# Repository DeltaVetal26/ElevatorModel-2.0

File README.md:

# ElevatorModel-2.0
Software and hardware for elevator model (STM32F3)

The first version of the elevator controller was assembled on the Arduino Pro Mini. Reed switches were used as floor sensors. The AC motor was controlled via a relay block.

The first version often freeze due to the lack of galvanic isolation

It was decided to develop a new version of the controller using galvanic isolation and based on the STM32F334K8T6 microcontroller.

Features:
1) The inputs on the board are isolated via optocouplers
2) The I2C bus responsible for outputting the current floor and reading the buttons is isolated through a digital isolator
3) A stepper motor is used as a drive
4) Optocouplers are used as floor sensors
5) The board has a step down converter (12V/3V3)

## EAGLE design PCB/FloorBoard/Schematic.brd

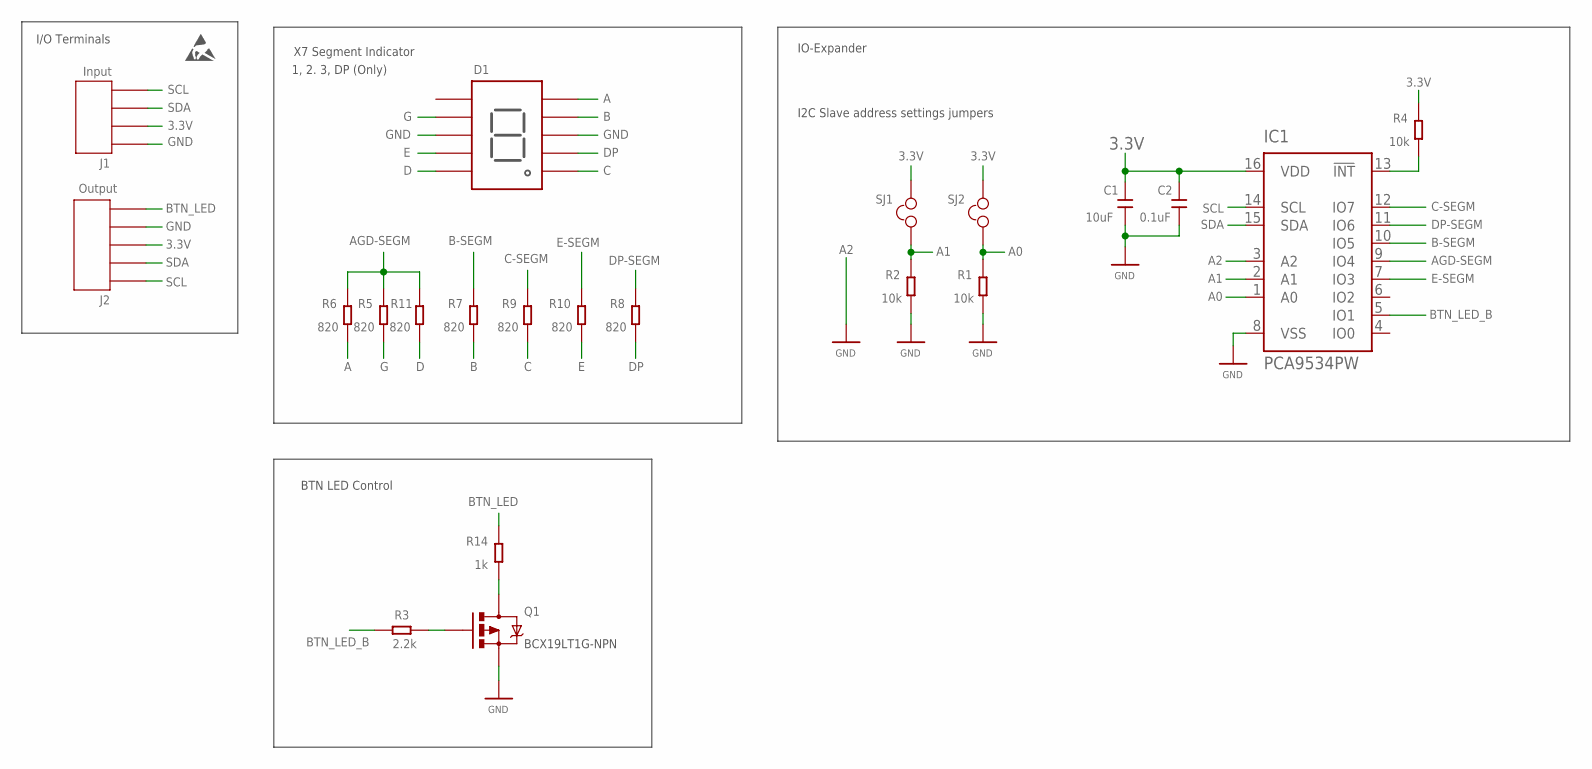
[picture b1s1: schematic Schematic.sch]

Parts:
C1: 10uF; SMD-CAP-0805
C2: 0.1uF; SMD-CAP-0805
D1: GNS-3011CS-21
IC1: PCA9534PW; TSSOP16
J1: Input; WF-4R
J2: Output; WF-5R
Q1: MOSFET-PCHANNEL; SOT23-3
R1, R2, R4: 10k; SMD-RES-0603
R3: 2.2k; SMD-RES-0603
R5, R6, R7, R8, R9, R10, R11: 820; SMD-RES-0603
R14: 1k; SMD-RES-0603
SJ1, SJ2: SOLDER-JUMPER
U$2: ESD-LOGO

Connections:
3.3V: C1.2, C2.2, IC1.16 (VDD), J1.P$2, J2.P$3, R4.2, SJ1.P$2, SJ2.P$2
A: D1.A, R6.1
A0: IC1.1 (A0), R1.2, SJ2.P$1
A1: IC1.2 (A1), R2.2, SJ1.P$1
A2: IC1.3 (A2)
AGD-SEGM: IC1.9 (IO4), R5.2, R6.2, R11.2
B: D1.B, R7.1
B-SEGM: IC1.10 (IO5), R7.2
BTN_LED: J2.P$5, R14.2
BTN_LED_B: IC1.5 (IO1), R3.2
C: D1.C, R9.1
C-SEGM: IC1.12 (IO7), R9.2
D: D1.D, R11.1
DP: D1.DP, R8.1
DP-SEGM: IC1.11 (IO6), R8.2
E: D1.E, R10.1
E-SEGM: IC1.7 (IO3), R10.2
G: D1.G, R5.1
GND: C1.1, C2.1, D1.CATHODE_1, D1.CATHODE_2, IC1.8 (VSS), J1.P$1, J2.P$4, Q1.2 (S), R1.1, R2.1
unnamed: IC1.13 (!INT), R4.1
unnamed: Q1.3 (D), R14.1
unnamed: Q1.1 (G), R3.1
SCL: IC1.14 (SCL), J1.P$4, J2.P$1
SDA: IC1.15 (SDA), J1.P$3, J2.P$2

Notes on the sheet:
I/O Terminals
X7 Segment Indicator
1, 2. 3, DP (Only)
IO-Expander
I2C Slave address settings jumpers
BCX19LT1G-NPN
BTN LED Control

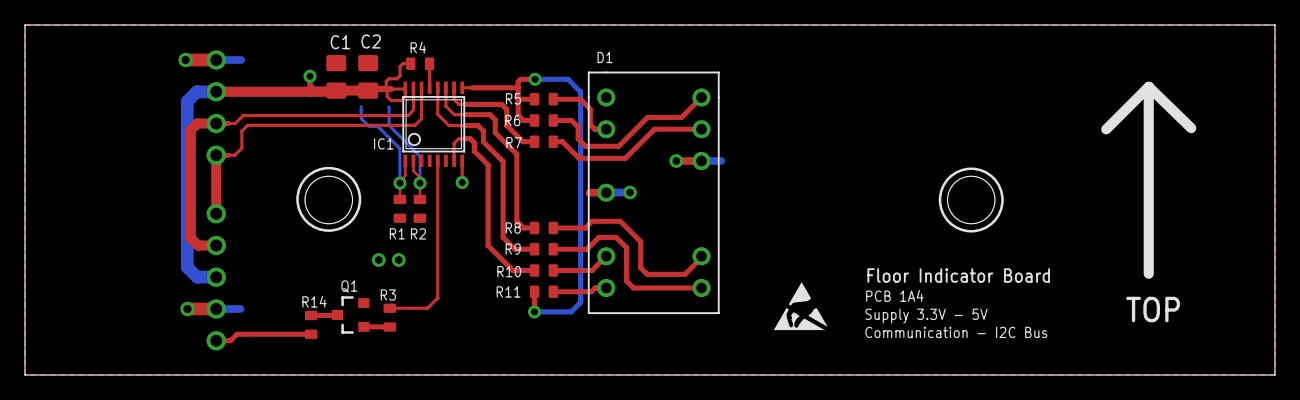
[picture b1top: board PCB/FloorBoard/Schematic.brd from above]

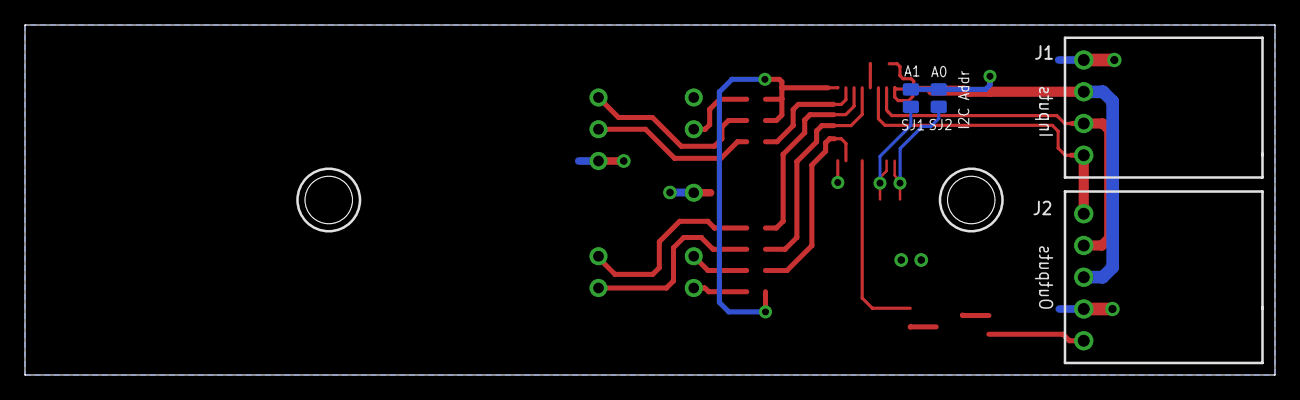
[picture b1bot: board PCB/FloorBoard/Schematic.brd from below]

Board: 2 copper layers, 100.0 x 28.0 mm, 22 parts (4 on the bottom side), 23 nets.

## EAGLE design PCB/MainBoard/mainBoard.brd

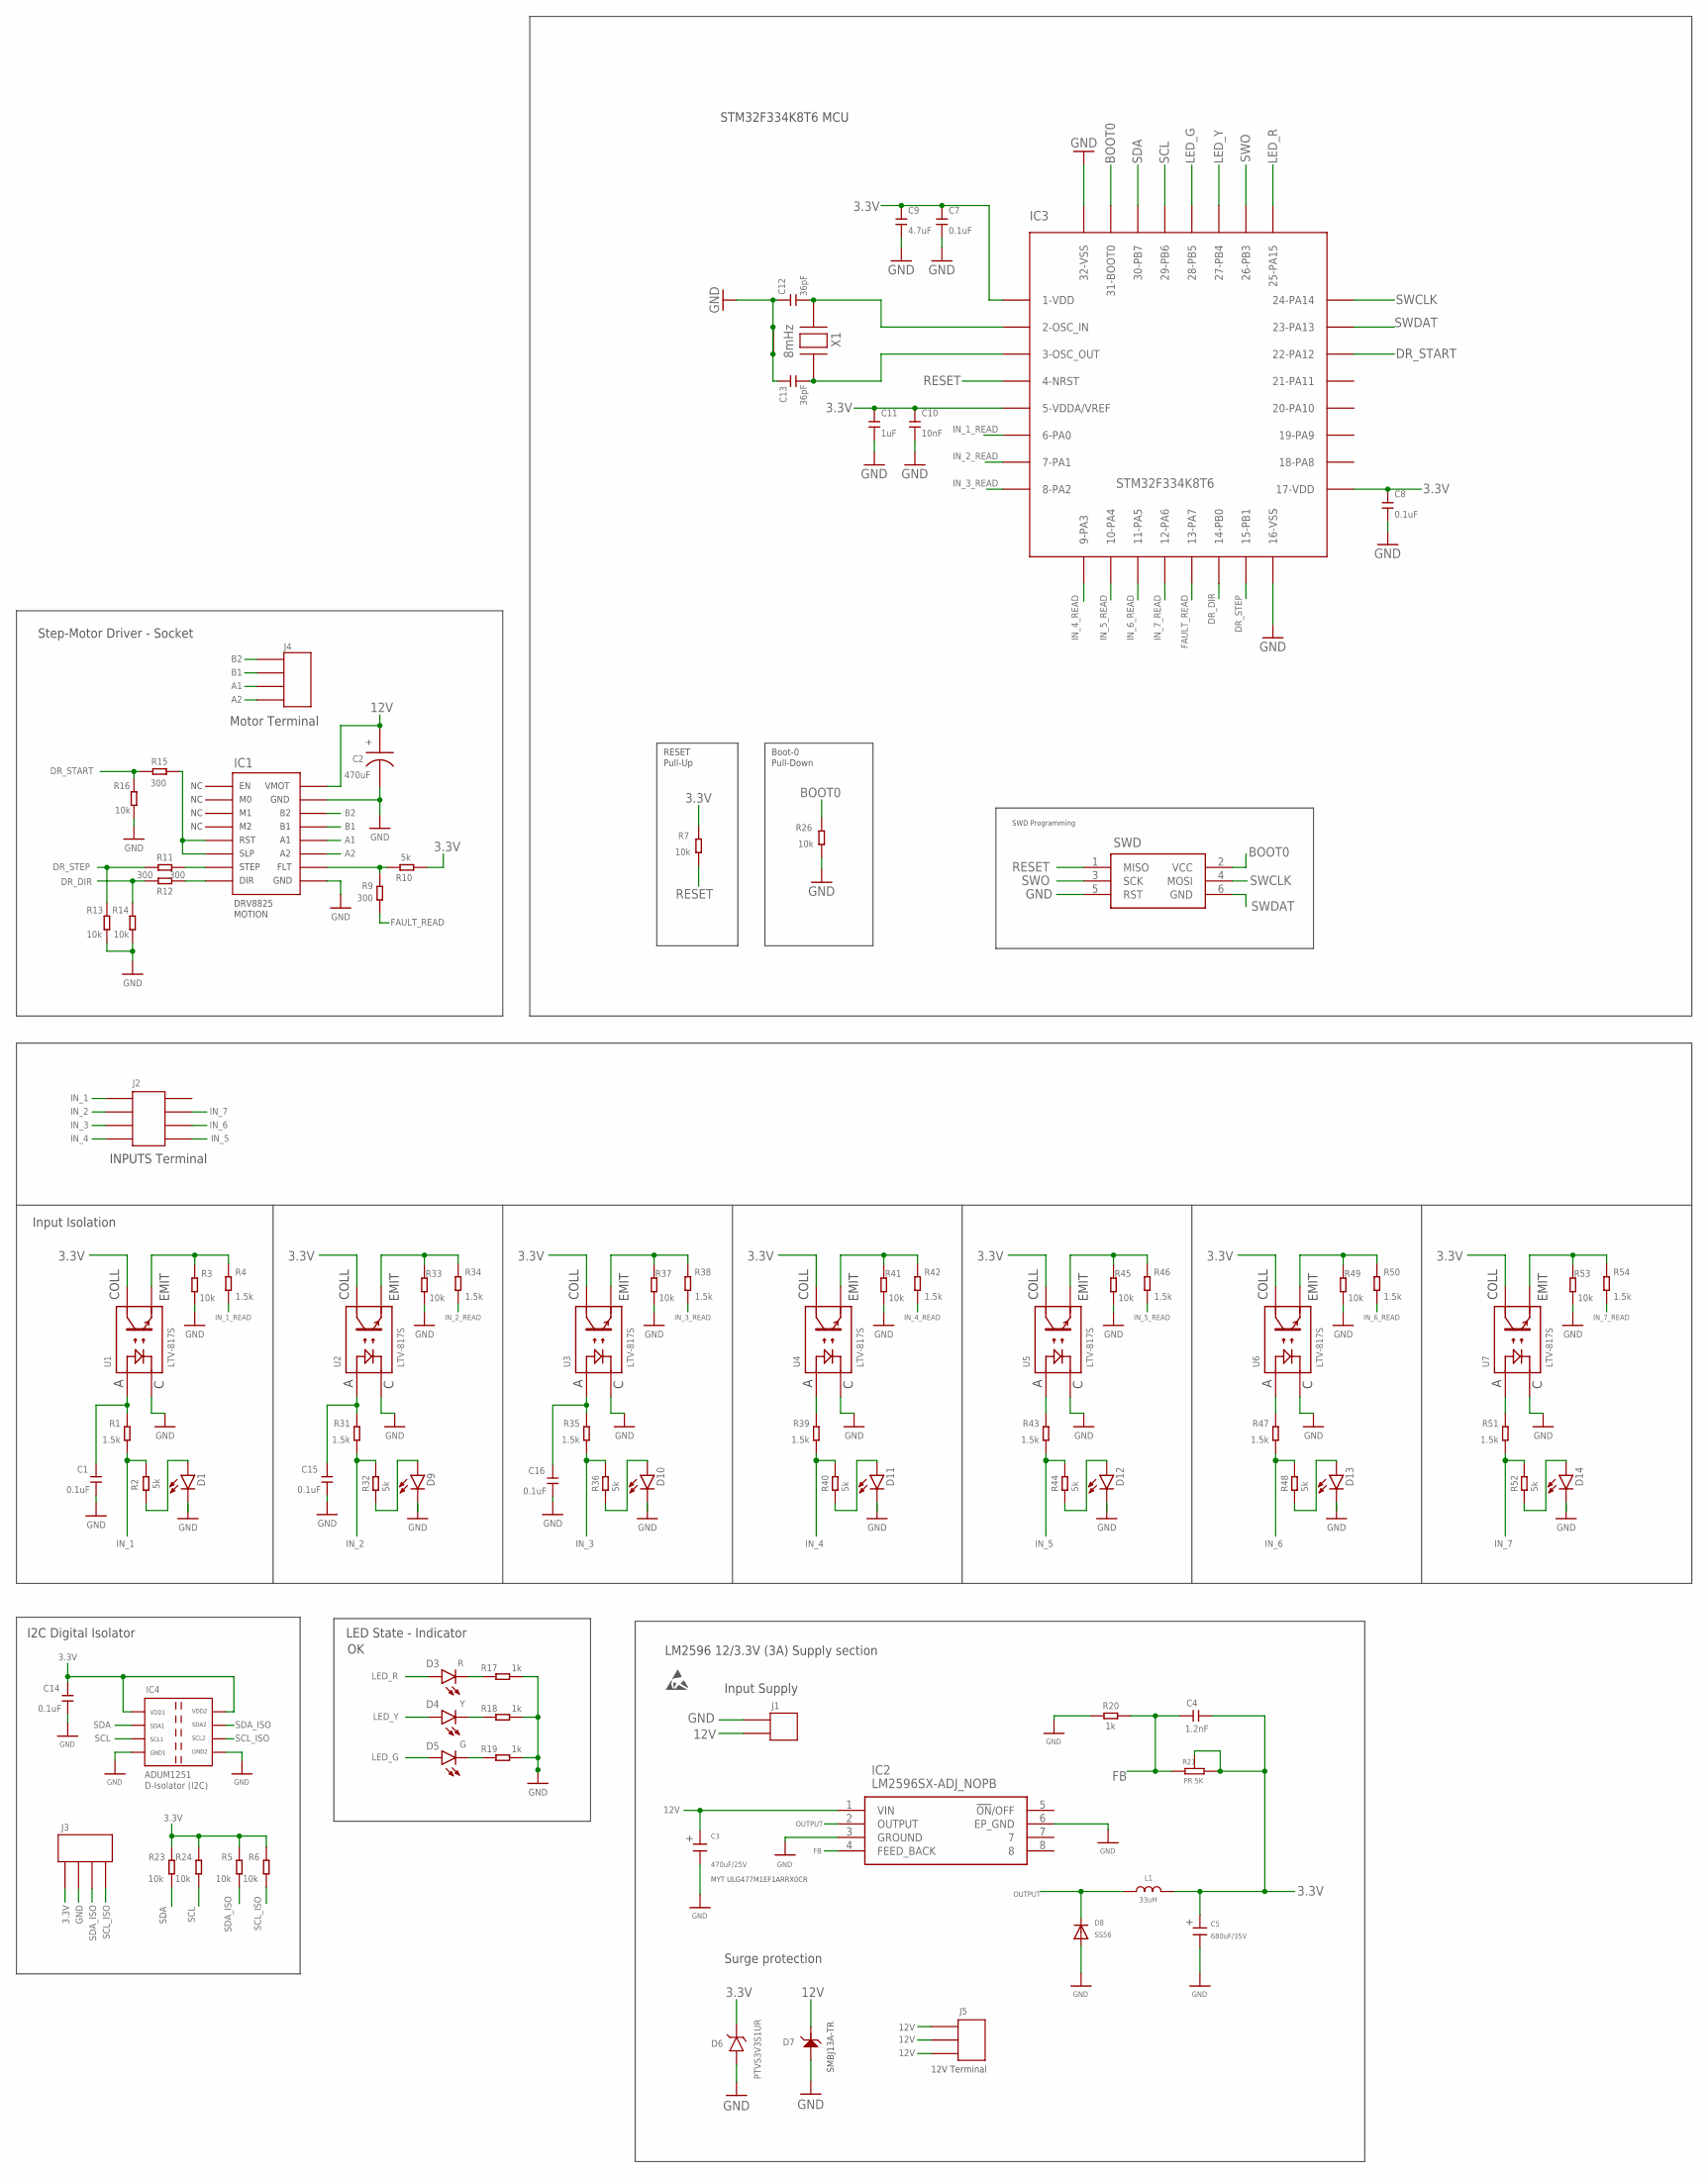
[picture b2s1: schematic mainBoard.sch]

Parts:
C1, C7, C8, C14, C15, C16: 0.1uF; SMD-CAP-0805
C2: 470uF; EPCOS-CAP-10X16
C3: MYT-680UF-25V-D8MM-F16
C4: 1.2nF; SMD-CAP-0805
C5: PANASONIC-SMT-CAP-680UF
C9: 4.7uF; SMD-CAP-0805
C10: 10nF; SMD-CAP-0805
C11: 1uF; SMD-CAP-0805
C12, C13: 36pF; SMD-CAP-0603
D1, D9, D10, D11, D12, D13, D14: LED0603; LED-0603
D3: R; LED-0603
D4: Y; LED-0603
D5: G; LED-0603
D6: PTVS3V3S1UR
D7: TVS-SMBJ13A-LFUSE
D8: S2A; DO214AA
IC1: DRV8825-DRIVER
IC2: LM2596SX-ADJ_NOPB; LM2596SXADJNOPB
IC3: STM32F334K8T6; QFP80P900X900X160-32N
IC4: ADUM1251ARZ-RL7
J1: DG127-5.0-2P
J2: 5EHDR-08P-5.00
J3, J4: DG127-5.0-4P
J5: PRESS-TERMINAL-5.0-3P
L1: SUNLTECHTEC-HSLO1365H330MTT
R1, R4, R31, R34, R35, R38, R39, R42, R43, R46, R47, R50, R51, R54: 1.5k; R0805
R2, R32, R36, R40, R44, R48, R52: 5k; SMD-RES-0603
R3, R5, R6, R13, R14, R16, R23, R24, R33, R37, R41, R45, R49, R53: 10k; R0805
R7, R26: 10k; SMD-RES-0603
R9, R11, R12, R15: 300; R0805
R10: 5k; R0805
R17, R18, R19: 1k; SMD-RES-0603
R20: 1k; R0805
R21: BOURNS-3296W-PREC-RESISTOR-5K
SWD: AVRISP-6; AVRISP
U1, U2, U3, U4, U5, U6, U7: LTV-817S
U$1: ESD-LOGO
X1: 8mHz; CRYSTALL-YTC-X50328MSB4SI

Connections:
3.3V: C4.2, C5.+, C7.2, C8.2, C9.2, C10.2, C11.2, C14.2, D6.C, IC3.1-VDD, IC3.5-VDDA/VREF, IC3.17-VDD, IC4.VDD1, IC4.VDD2, J3.P$1, L1.P$2, R5.2, R6.2, R7.2, R10.2, R21.CW-3, R21.WIPER-2, R23.2, R24.2, U1.COLL (COLLECTOR), U2.COLL (COLLECTOR), U3.COLL (COLLECTOR), U4.COLL (COLLECTOR), U5.COLL (COLLECTOR), U6.COLL (COLLECTOR), U7.COLL (COLLECTOR)
12V: C2.+, C3.+, D7.-, IC1.VMOT, IC2.1 (VIN), J1.P$2, J5.A1, J5.A2, J5.A3, J5.B1, J5.B2, J5.B3
A1: IC1.A1, J4.P$3
A2: IC1.A2, J4.P$4
B1: IC1.B1, J4.P$2
B2: IC1.B2, J4.P$1
BOOT0: IC3.31-BOOT0, R26.2, SWD.2 (VCC)
DR_DIR: IC3.14-PB0, R12.1, R14.2
DR_START: IC3.22-PA12, R15.1, R16.2
DR_STEP: IC3.15-PB1, R11.1, R13.2
FAULT_READ: IC3.13-PA7, R9.2
FB: C4.1, IC2.4 (FEED_BACK), R20.2, R21.CCW-1
GND: C1.1, C2.-, C3.-, C5.-, C7.1, C8.1, C9.1, C10.1, C11.1, C12.1, C13.1, C14.1, C15.1, C16.1, D1.C, D6.A, D7.+, D8.A, D9.C, D10.C, D11.C, D12.C, D13.C, D14.C, IC1.GND, IC1.GND_1, IC2.3 (GROUND), IC2.6 (EP_GND), IC3.16-VSS, IC3.32-VSS, IC4.GND1, IC4.GND2, J1.P$1, J3.P$2, R3.2, R13.1, R14.1, R16.1, R17.1, R18.1, R19.1, R20.1, R26.1, R33.2, R37.2, R41.2, R45.2, R49.2, R53.2, SWD.5 (RST), U1.C, U2.C, U3.C, U4.C, U5.C, U6.C, U7.C, X1.2 (G1), X1.4 (G2)
IN_1: J2.1, R1.1, R2.2
IN_1_READ: IC3.6-PA0, R4.2
IN_2: J2.2, R31.1, R32.2
IN_2_READ: IC3.7-PA1, R34.2
IN_3: J2.3, R35.1, R36.2
IN_3_READ: IC3.8-PA2, R38.2
IN_4: J2.4, R39.1, R40.2
IN_4_READ: IC3.9-PA3, R42.2
IN_5: J2.5, R43.1, R44.2
IN_5_READ: IC3.10-PA4, R46.2
IN_6: J2.6, R47.1, R48.2
IN_6_READ: IC3.11-PA5, R50.2
IN_7: J2.7, R51.1, R52.2
IN_7_READ: IC3.12-PA6, R54.2
LED_G: D5.A, IC3.28-PB5
LED_R: D3.A, IC3.25-PA15
LED_Y: D4.A, IC3.27-PB4
unnamed: D1.A, R2.1
unnamed: R3.1, R4.1, U1.EMIT (EMITTER)
unnamed: IC1.STEP, R11.2
unnamed: IC1.FAULT, R9.1, R10.1
unnamed: IC1.DIR, R12.2
unnamed: D3.C, R17.2
unnamed: IC1.RST, IC1.SLEEP, R15.2
unnamed: D4.C, R18.2
unnamed: D5.C, R19.2
unnamed: C12.2, IC3.2-OSC_IN, X1.3
unnamed: C13.2, IC3.3-OSC_OUT, X1.1
unnamed: C15.2, R31.2, U2.A
unnamed: D9.A, R32.1
unnamed: R33.1, R34.1, U2.EMIT (EMITTER)
unnamed: C16.2, R35.2, U3.A
unnamed: D10.A, R36.1
unnamed: R37.1, R38.1, U3.EMIT (EMITTER)
unnamed: R39.2, U4.A
unnamed: D11.A, R40.1
unnamed: R41.1, R42.1, U4.EMIT (EMITTER)
unnamed: R43.2, U5.A
unnamed: D12.A, R44.1
unnamed: R45.1, R46.1, U5.EMIT (EMITTER)
unnamed: R47.2, U6.A
unnamed: D13.A, R48.1
unnamed: R49.1, R50.1, U6.EMIT (EMITTER)
unnamed: R51.2, U7.A
unnamed: D14.A, R52.1
unnamed: R53.1, R54.1, U7.EMIT (EMITTER)
unnamed: C1.2, R1.2, U1.A
OUTPUT: D8.C, IC2.2 (OUTPUT), L1.P$1
RESET: IC3.4-NRST, R7.1, SWD.1 (MISO)
SCL: IC3.29-PB6, IC4.SCL1, R24.1
SCL_ISO: IC4.SCL2, J3.P$4, R6.1
SDA: IC3.30-PB7, IC4.SDA1, R23.1
SDA_ISO: IC4.SDA2, J3.P$3, R5.1
SWCLK: IC3.24-PA14, SWD.4 (MOSI)
SWDAT: IC3.23-PA13, SWD.6 (GND)
SWO: IC3.26-PB3, SWD.3 (SCK)

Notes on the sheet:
Input Isolation
Step-Motor Driver - Socket
LED State - Indicator
Surge protection
SMBJ13A-TR
470uF/25V
SS56
33uH
680uF/35V
PR 5K
MYT ULG477M1EF1ARRX0CR
LM2596 12/3.3V (3A) Supply section
STM32F334K8T6 MCU
RESET
Pull-Up
Boot-0
Pull-Down
SWD Programming
I2C Digital Isolator
Input Supply
INPUTS Terminal
Motor Terminal
12V Terminal

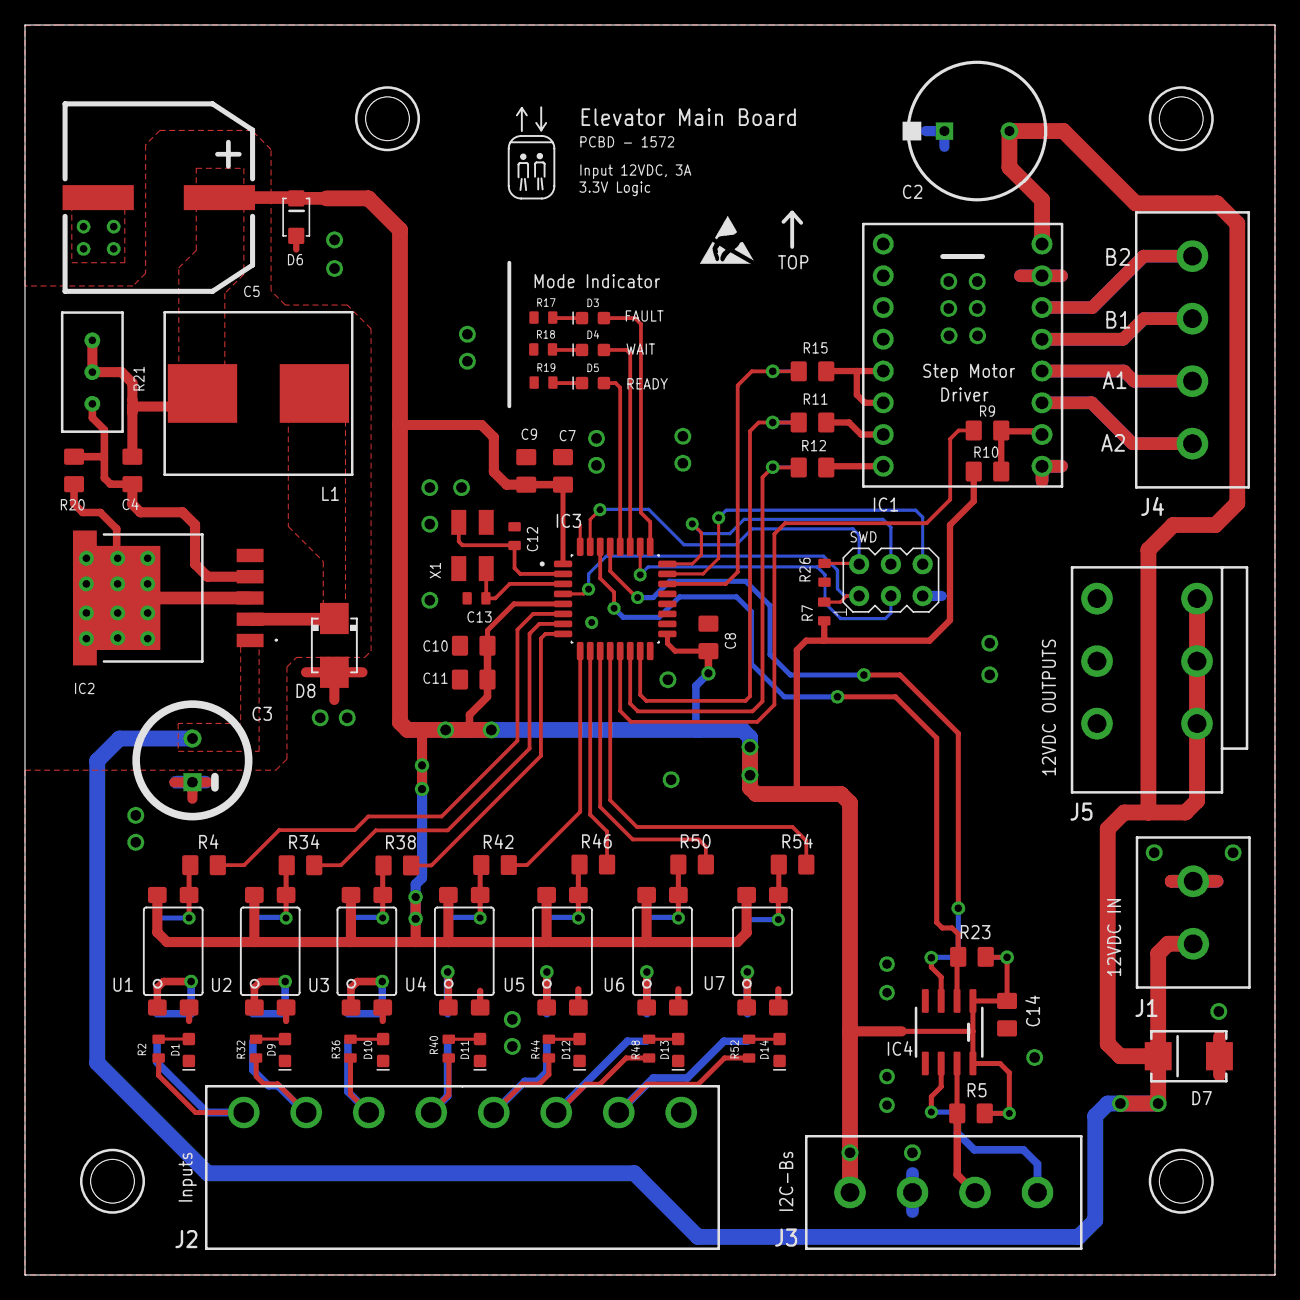
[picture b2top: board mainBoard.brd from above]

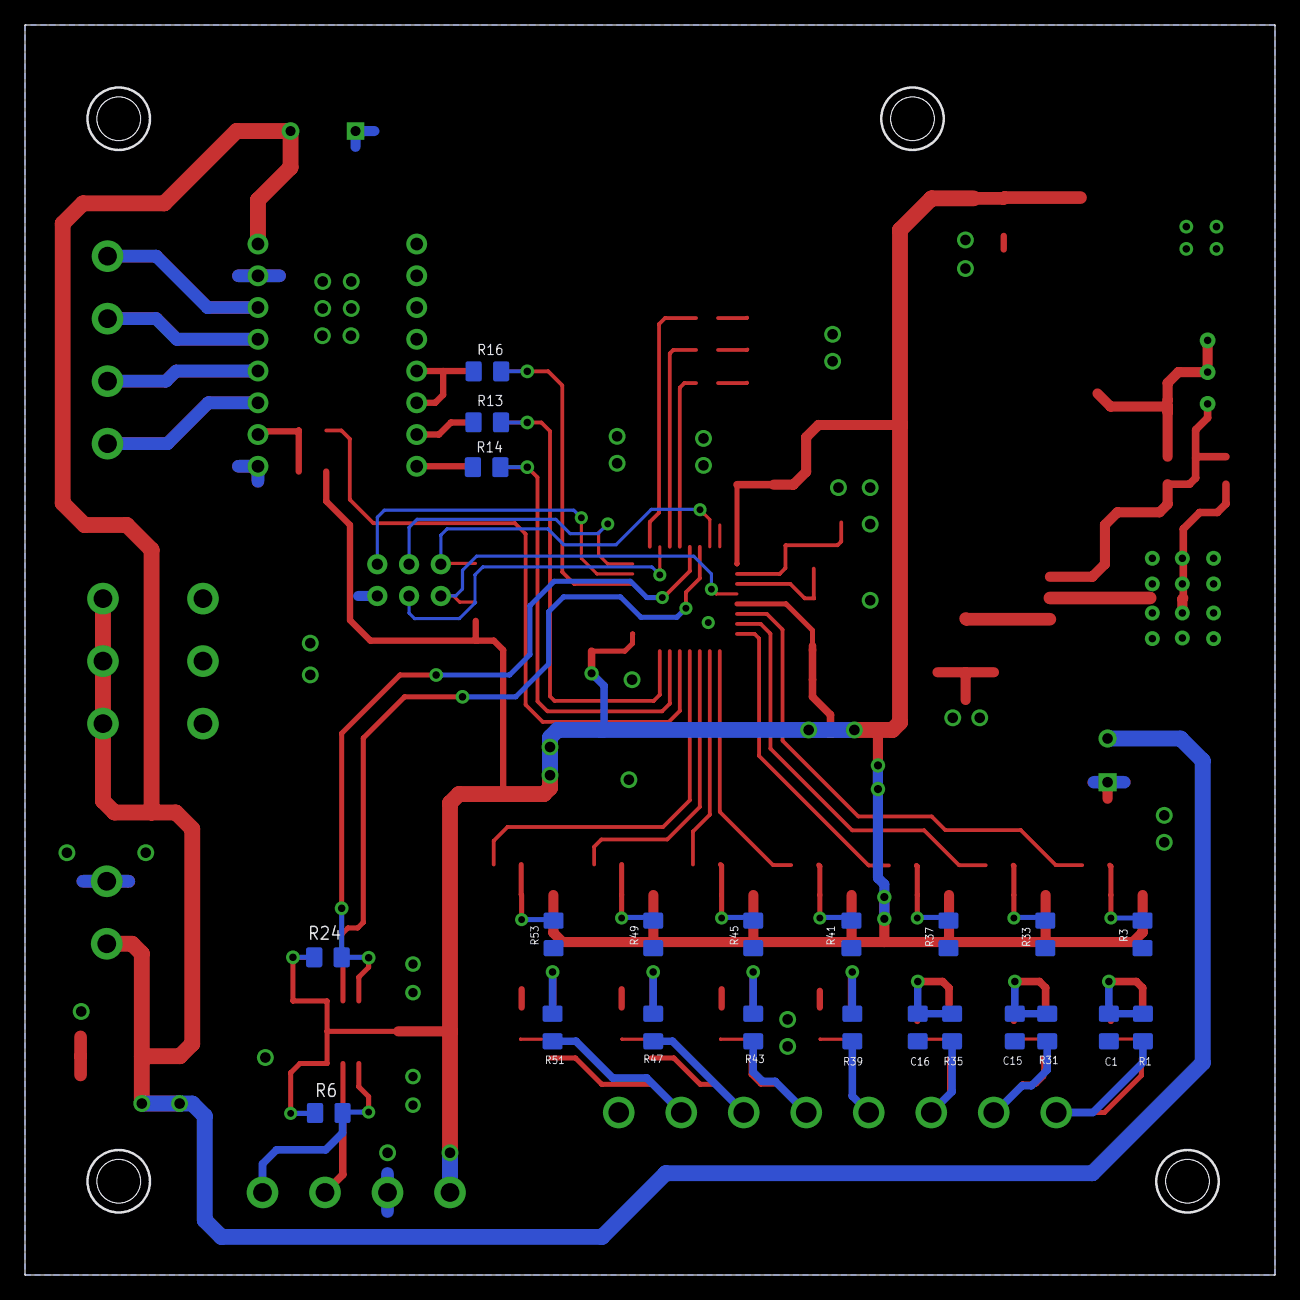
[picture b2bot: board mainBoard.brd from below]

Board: 2 copper layers, 100.0 x 100.0 mm, 95 parts (22 on the bottom side), 69 nets.

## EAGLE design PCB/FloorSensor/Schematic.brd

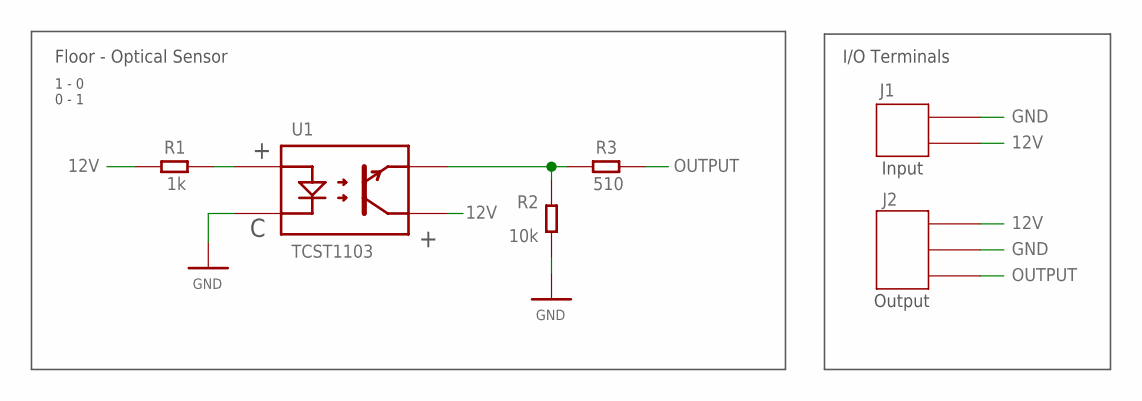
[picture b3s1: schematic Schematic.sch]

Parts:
J1: WF-2R
J2: WF-3R
R1: 1k; SMD-RES-0603
R2: 10k; SMD-RES-0603
R3: 510; SMD-RES-0603
U1: TCST1103

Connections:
12V: J1.P$1, J2.P$3, R1.2, U1.OUTPUT_VCC
GND: J1.P$2, J2.P$2, R2.2, U1.INPUT_C (C)
unnamed: R1.1, U1.INPUT_VCC
unnamed: R2.1, R3.2, U1.OUTPUT
OUTPUT: J2.P$1, R3.1

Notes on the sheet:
Floor - Optical Sensor
1 - 0
0 - 1
Input
Output
I/O Terminals

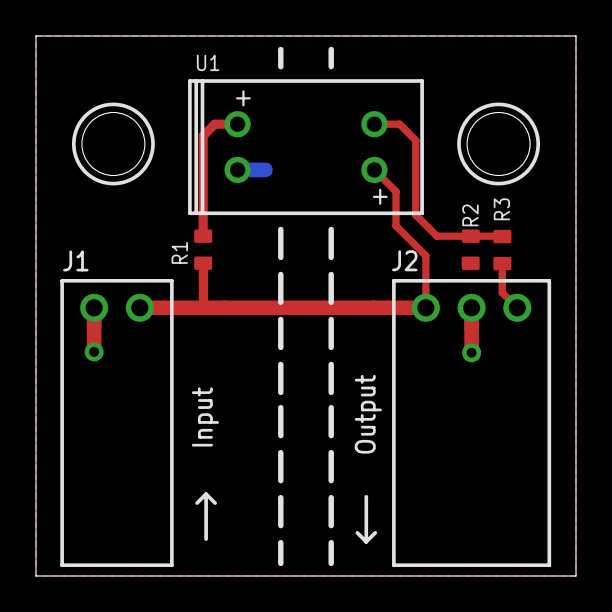
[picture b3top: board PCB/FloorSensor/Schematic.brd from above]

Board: 2 copper layers, 30.0 x 30.0 mm, 6 parts (0 on the bottom side), 5 nets.

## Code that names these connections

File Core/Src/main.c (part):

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#define HIGH 1
#define LOW  0
// PORT A used pins
#define PA0   0
#define PA1   1
#define PA2   2
#define PA3   3
#define PA4   4
#define PA5   5
#define PA6   6
#define PA7   7
#define PA12  8
#define PA15  9
// PORT B used pins
#define PB0  10
#define PB1  11
#define PB4  12
#define PB5  13
// PORT ID
#define PORT_A 0
#define PORT_B 1
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// PORT / Pin ID, Pin number
uint8_t pinInfoArr[][3] = {
  // PORTA
  {PORT_A, 0, 6},    // PA0
  {PORT_A, 1, 7},    // PA1
  {PORT_A, 2, 8},    // PA2
  {PORT_A, 3, 9},    // PA3
  {PORT_A, 4, 10},   // PA4
  {PORT_A, 5, 11},   // PA5
  {PORT_A, 6, 12},   // PA6
  {PORT_A, 7, 13},   // PA7
  {PORT_A, 12, 22},  // PA12
  {PORT_A, 15, 25},  // PA15
  // PORTB
  {PORT_B, 0, 14},   // PB0
  {PORT_B, 1, 15},   // PB1
  {PORT_B, 4, 27},   // PB4
  {PORT_B, 5, 28},   // PB5
};

// state indicator
#define RED_LED     PA15
#define YELLOW_LED  PB4
#define GREEN_LED   PB5
#define STATIC 1
#define BLINK  2
#define CLEAR  3
#define defBlinkTime 800

// Motion drive
#define mStepPin         PB1
#define mDirectionPin    PB0
#define mDriveStartPin   PA12
#define mDefaultHTime    80
#define mDefaultSpeed    140 // 140 step per x1 sec
#define mLowSpeed        60  // 60 step per x1 sec (for calibrate mode)
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
// ### PIN control ###
// # Set pin mode
// Ex: pinControl_SetMode(28, OUTPUT); - set PB5 to OUTPUT mode
void pinControl_setMode(unsigned pin, unsigned mode) {
  uint8_t pinArrPort = pinInfoArr[pin][0];
  uint8_t pinArrID = pinInfoArr[pin][1];
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  }
}
// # Set pin speed
// Ex: pinControl_SetSpeed(GPIOB, 5, 01); - set PB5 to Medium speed
void pinControl_setSpeed(unsigned pin, unsigned speed) {
  uint8_t pinArrPort = pinInfoArr[pin][0];
  uint8_t pinArrID = pinInfoArr[pin][1];
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  }
}
// # Set pin state
// Ex: pinControl_SetState(28, HIGH); - set PB5 to HIGH state
void pinControl_setState(unsigned pin, unsigned mode) {
  uint8_t pinArrPort = pinInfoArr[pin][0];
  uint8_t pinArrID = pinInfoArr[pin][1];
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  }
}
// # Get pin state
// Ex: pinControl_getState(PB5); - get PB5 state
/*uint8_t pinControl_getState(unsigned pin) {
  uint8_t pinArrPort = pinInfoArr[pin][0];
  uint8_t pinArrNumber = pinInfoArr[pin][2];
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    // stage #1 - HIGH
    if((stageNumber == 1) && (micros() - usTimer >= mDrive_VAR_mLowTime)) {
      stageNumber = 0;
      // set HIGH state to step pin (PB1)
      GPIOB->BSRR |= (BITMASK(1) << (1 * MotorStepPin_Local));
      usTimer = micros();
    }
    // stage #2 - LOW
    if((stageNumber == 0) && (micros() - usTimer >= mDrive_VAR_mHighTime)) {
      stageNumber = 1;
      // set LOW state to step pin (PB1)
      GPIOB->BSRR |= (BITMASK(1) << (1 * 16 + MotorStepPin_Local));
      usTimer = micros();
    }
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  __HAL_RCC_GPIOB_CLK_ENABLE();
  __HAL_RCC_GPIOA_CLK_ENABLE();

  /*Configure GPIO pins : PA0 PA1 PA2 PA3 PA4 PA5 PA6 */
  GPIO_InitStruct.Pin = GPIO_PIN_0|GPIO_PIN_1|GPIO_PIN_2|GPIO_PIN_3|GPIO_PIN_4|GPIO_PIN_5|GPIO_PIN_6;
  GPIO_InitStruct.Mode = GPIO_MODE_INPUT;
  GPIO_InitStruct.Pull = GPIO_NOPULL;
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
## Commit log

2021-07-06 Upload files
2021-11-16 Add new files (photo)

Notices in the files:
parts and their libraries:
User-Submitted: Licensing: Creative Commons ShareAlike 4.0 International - https://creativecommons.org/licenses/by-sa/4.0
